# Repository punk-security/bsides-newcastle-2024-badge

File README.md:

# BSides Newcastle (2024) Plant badge (Little Shop of Horrors)

**This badge was given out at BSIDES Newcastle and it's a working soil sensor!**

This badge uses UV full colour silk, and we ordered them from JLCPCB using EasyEDA. The PCB was built first with AutoCAD EAGLE, then exported.

Lots of things in this repo:

- eagle-files: all the stuff you need to tinker and modify the PCB in AutoCAD Eagle
- bsides-newcastle-2024.epro - The EasyEDA export, including the front and back art 
- gerber.zip: the file you can upload to JLCPCB and order your own badge, as is
- bsides-newcastle-2024-badge.ino: the arduino code that powers the badge, which you can modify and flash via the SAO connector

## Bill Of Materials

You can see a parts list on DigiKey [here](https://www.digikey.co.uk/en/mylists/list/1SMRGQW6IU).

Essentially its:

* ATTINY402 microcontroller
* Button - any surface mount button fitting the footprint will work
* CR2032 battery clip  - surface mount not through hole
* Neopixel 5050 addressable LED - Definitely get the right version of these
* Resistor - 6.8K 1206 resistor 

## How does it work?

The bottom of the badge (the pot) has 2 big copper pads under the artwork. Together, these act like a very tiny battery. 

This "battery" charges a little bit slower when surrounded by wet soil.

We start to charge the battery with one pin from the attiny402, and measure how charged it is with another.

This would be pretty much instant, so we slow down the charging with a resistor.

Watch my talk on the madness of developing this badge: https://www.youtube.com/watch?v=vW9SHSsYLkk

## Eagle designs and ordering your own badge

We've uploaded the AutoCAD EAGLE schematic and board design!  You will probably have to do some tweaks to get it working as they're not designed to be standalone exports.

This is then exported to EasyEDA to add the colour print to the boards. The file for that is already in the repo, so you can skip the EAGLE step if you prefer.

We've also uploaded the gerber.zip.  Take this to JLCPCB and you can order your own exact copies of the board :)

## Writing and flashing code!

We use [MegaTinyCore](https://github.com/SpenceKonde/megaTinyCore) for the arduino interface for ATTINY4x2 chips.

Dev and flashing is done within the Arduino IDE ( < v2 ) using a jtag2updi interface, as discussed [here](https://github.com/SpenceKonde/AVR-Guidance/blob/master/UPDI/jtag2updi.md)

We use [these little usb sticks](https://amzn.eu/d/c0lx0wG), with a 4.7k resistor soldered between the Tx and Rx lines.  

### Installing MegaTinyCore dependencies

This board package can be installed via the board manager in arduino. The boards manager URL is:

`http://drazzy.com/package_drazzy.com_index.json`

1. File -> Preferences, enter the above URL in "Additional Boards Manager URLs"
2. Tools -> Boards -> Boards Manager...
3. Wait while the list loads (takes longer than one would expect, and refreshes several times).
4. Select "megaTinyCore by Spence Konde" and click "Install". For best results, choose the most recent version.

### Setting up the IDE

1. Open the file **bsides-newcastle-2024-badge.ino** in arduino
2. Select tools > Board > megaTinyCore > ATtiny412/402/212/202
3. Select tools > Chip > ATtiny402
4. Select tools > Clock > 8Mhz internal *(we get power issues otherwise)*
5. Select tools > Programmer > SerialUPDI SLOW
6. Select tools > Port > ( pick your COM port)

### Flashing firmware
1. Connect the 3v3 pin to 3v on your usb (maybe wedge it in the battery clip)
2. Connect GND to GND
3. Connect UPDI to the RxD port
4. Click Upload button

## How to solder?

Make sure to line up the dot on the attiny402 with the dot on the board.

Make sure to line the corner of the LED with the cutout with the triangle on the board

*It's much easier if you hold the component in place with one hand, and then solder one pad. Now you can solder the rest of the pads with one hand*

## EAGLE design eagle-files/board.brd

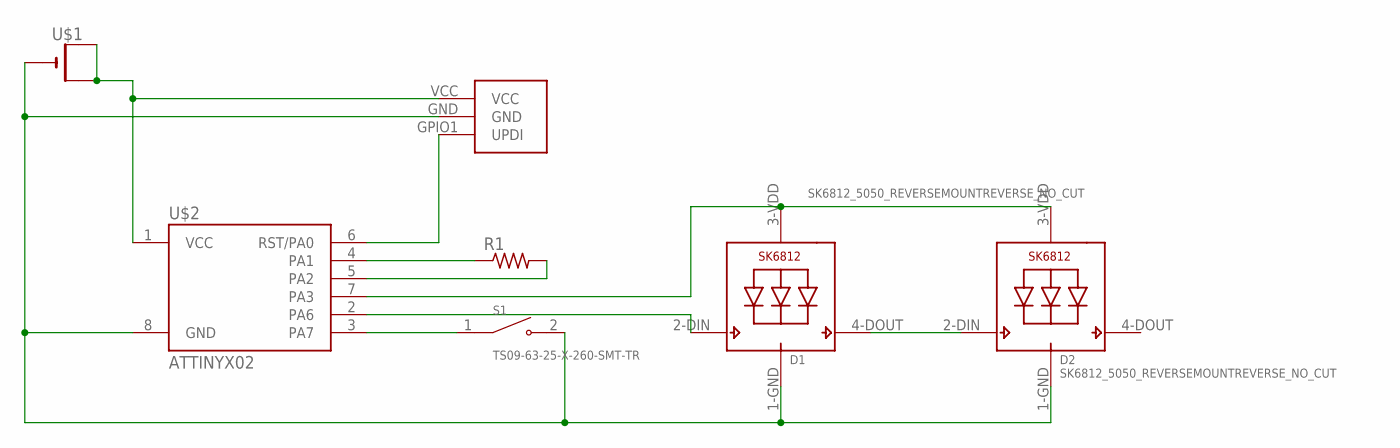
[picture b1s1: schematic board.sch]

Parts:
D1, D2: SK6812_5050_REVERSEMOUNTREVERSE_NO_CUT; SK6812_REVERSE_NO_CUT
R1: R-US_R1206; R1206
S1: TS09-63-25-X-260-SMT-TR; SW_TS09-63-25-X-260-SMT-TR
U$1: CR2032SMT; CR2032-SMD
U$2: ATTINYX02; SOIC08_JEDEC_150MIL
U$3: SAO; SAO_SMD

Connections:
unnamed: U$1.+$1 (+), U$1.+$2 (+1), U$2.1 (VCC), U$3.VCC
unnamed: D1.1-GND (GND), D2.1-GND (GND), S1.2, U$1.-, U$2.8 (GND), U$3.GND
unnamed: R1.1, U$2.4 (PA1)
unnamed: S1.1, U$2.3 (PA7)
unnamed: D1.2-DIN (DI), U$2.2 (PA6)
unnamed: D1.4-DOUT (DO), D2.2-DIN (DI)
unnamed: D1.3-VDD (VDD), D2.3-VDD (VDD), U$2.7 (PA3)
unnamed: U$2.6 (RST/PA0), U$3.GPIO1 (UPDI)
SENSE: R1.2, U$2.5 (PA2)

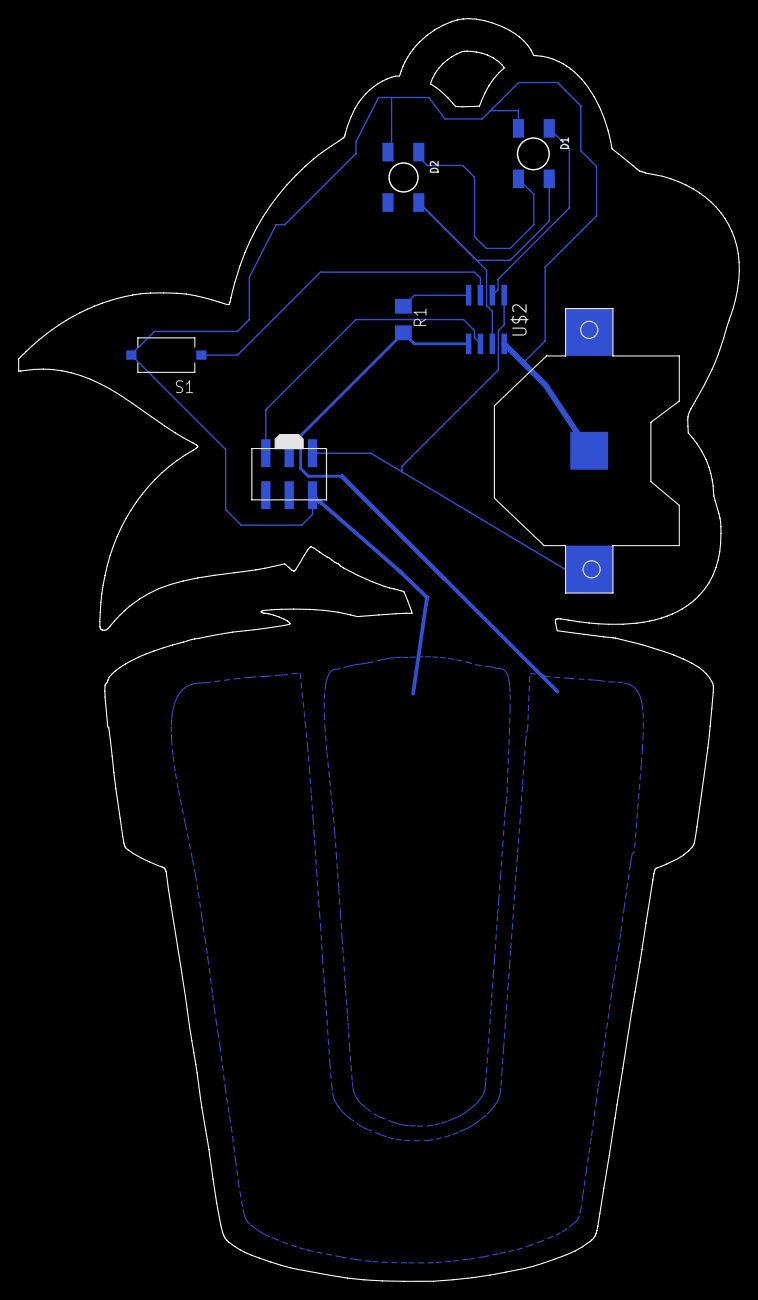
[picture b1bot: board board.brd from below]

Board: 2 copper layers, 77.1 x 135.1 mm, 7 parts (7 on the bottom side), 9 nets.

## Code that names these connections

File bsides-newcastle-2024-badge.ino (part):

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#include <tinyNeoPixel_Static.h>
#define NUMLEDS 2
byte pixels[NUMLEDS * 3];
tinyNeoPixel strip = tinyNeoPixel(NUMLEDS, PIN_PA6, NEO_GRB, pixels);

typedef struct AnalogReadResult {
    int16_t minValue;
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    int16_t delta;
};

#define BUTTON_PIN PIN_PA7

uint16_t time_pin_low(uint16_t max_ms)
{
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  PORTA.PIN7CTRL = PORT_PULLUPEN_bm | PORT_ISC_LEVEL_gc; // enable pullup and interrupt
  // TODO, sleep timer interrupt...
  // Turn off pins
  digitalWrite(PIN_PA3, LOW); // turn off LED power rail
  pinMode(PIN_PA2, OUTPUT);   // stop sense pin floating
  // Disable other power draining things
  ADC0.CTRLA &= ~ADC_ENABLE_bm; // disable adc
  // Enter sleep
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  // Remove interrupts
  PORTA.PIN7CTRL = PORT_PULLUPEN_bm; // renable pullup but no interrupt
  // Setup pins
  pinMode(PIN_PA2, INPUT);   // turn sense pin to input
  // Renable ADC
  ADC0.CTRLA |= ADC_ENABLE_bm; // enable ADC
}
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void setup()
{
  // Setup pins
  pinMode(PIN_PA1, OUTPUT);       // PWM
  pinMode(PIN_PA2, INPUT);        // SENSE
  pinMode(PIN_PA3, OUTPUT);       // LED PWR
  pinMode(PIN_PA6, OUTPUT);       // LED DATA
  pinMode(PIN_PA7, INPUT_PULLUP); // BUTTON
  // Set analog sample furation
  analogSampleDuration(1);
  // Enable serial
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AnalogReadResult sense()
{
    AnalogReadResult result;
    analogRead(PIN_PA2); // Take and throw away a reading
    analogWrite(PIN_PA1, 128); // Enable PWM with 50% duty cycle
    delayMicroseconds(200); // Wait 10ms
    result.maxValue = 0;
    result.minValue = 1024;
    int16_t value = 0;
    for (int i = 0; i < 200; i++) {
      value = analogRead(PIN_PA2);
      if (value > result.maxValue) { result.maxValue = value; } // Update maxValue
      if (value < result.minValue) { result.minValue = value; } // Update minValue
    }
    digitalWrite(PIN_PA1, LOW); // Disable PWM
    result.delta = result.maxValue - result.minValue;
    return result;
}
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
AnalogReadResult sense2() // This takes about 3ms to read
{
    analogWrite(PIN_PA1, 128); // Enable PWM with 50% duty cycle
    ADC0.MUXPOS=0x02; //reads from PA6/arduino pin 2, ADC0 channel 6
    ADC0.CTRLA=ADC_ENABLE_bm|ADC_FREERUN_bm; //start in freerun 
    ADC0.COMMAND=ADC_STCONV_bm; //start first conversion!
    AnalogReadResult result;
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      if (value > result.maxValue) { result.maxValue = value; } // Update maxValue
      if (value < result.minValue) { result.minValue = value; } // Update minValue
    }
    digitalWrite(PIN_PA1, LOW); // Disable PWM
    ADC0.CTRLA = ~ADC_ENABLE_bm; // Disable ADC
    result.delta = result.maxValue - result.minValue;
    return result;    
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
void flash(int r, int g, int b, uint16_t ms = 3000, int count = 1)
{
  digitalWriteFast(PIN_PA3, HIGH);
  strip.setPixelColor(LEFT, OFF);
  strip.setPixelColor(RIGHT, OFF);
  strip.show();
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        interval = 0;
        return;
      }
      digitalWriteFast(PIN_PA3,HIGH);
      delay(1);
      if (interval != 0) 
      {
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
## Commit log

2025-08-20 init
2025-08-20 init (#1)
2025-08-20 typo
